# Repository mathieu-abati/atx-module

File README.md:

# RaspberryPi ATX PSU control module

With an ATX PSU powering a RaspberryPi, this circuit allows to control power ON / OFF from a single posh button.

More details [on the project official page](https://mathieu-abati.com/en/projects/atx-module/).

## Compatibility

| Board                  | Tested | Working    |
| ---------------------- | ------ | ---------- |
| RaspberryPi 3 Model B  | ✅     | ✅         |
| RaspberryPi 3 Model B+ | ✅     | ✅         |
| RaspberryPi 4 2GB      | ✅     | ✅         |
| RaspberryPi 5 2GB      | ✅     | ❌         |

On RaspberryPi 5, power supply from extension connector is more complicated and is not working as-is with this module.

## Additional resources

For simulation, 2N2222A spice model file is not provided here du to license restrictions. You can download it
[from onSemi website](https://www.onsemi.com/download/models/txt/2n2222a.lib.txt),
and save it as `models/2N2222A.lib`.

For PCB 3D view, you may want the `ATX Connector 24pin 90deg.stp` file. You can
find it from [Grabcad](https://grabcad.com/library/90-atx-connector-24-pins-1).

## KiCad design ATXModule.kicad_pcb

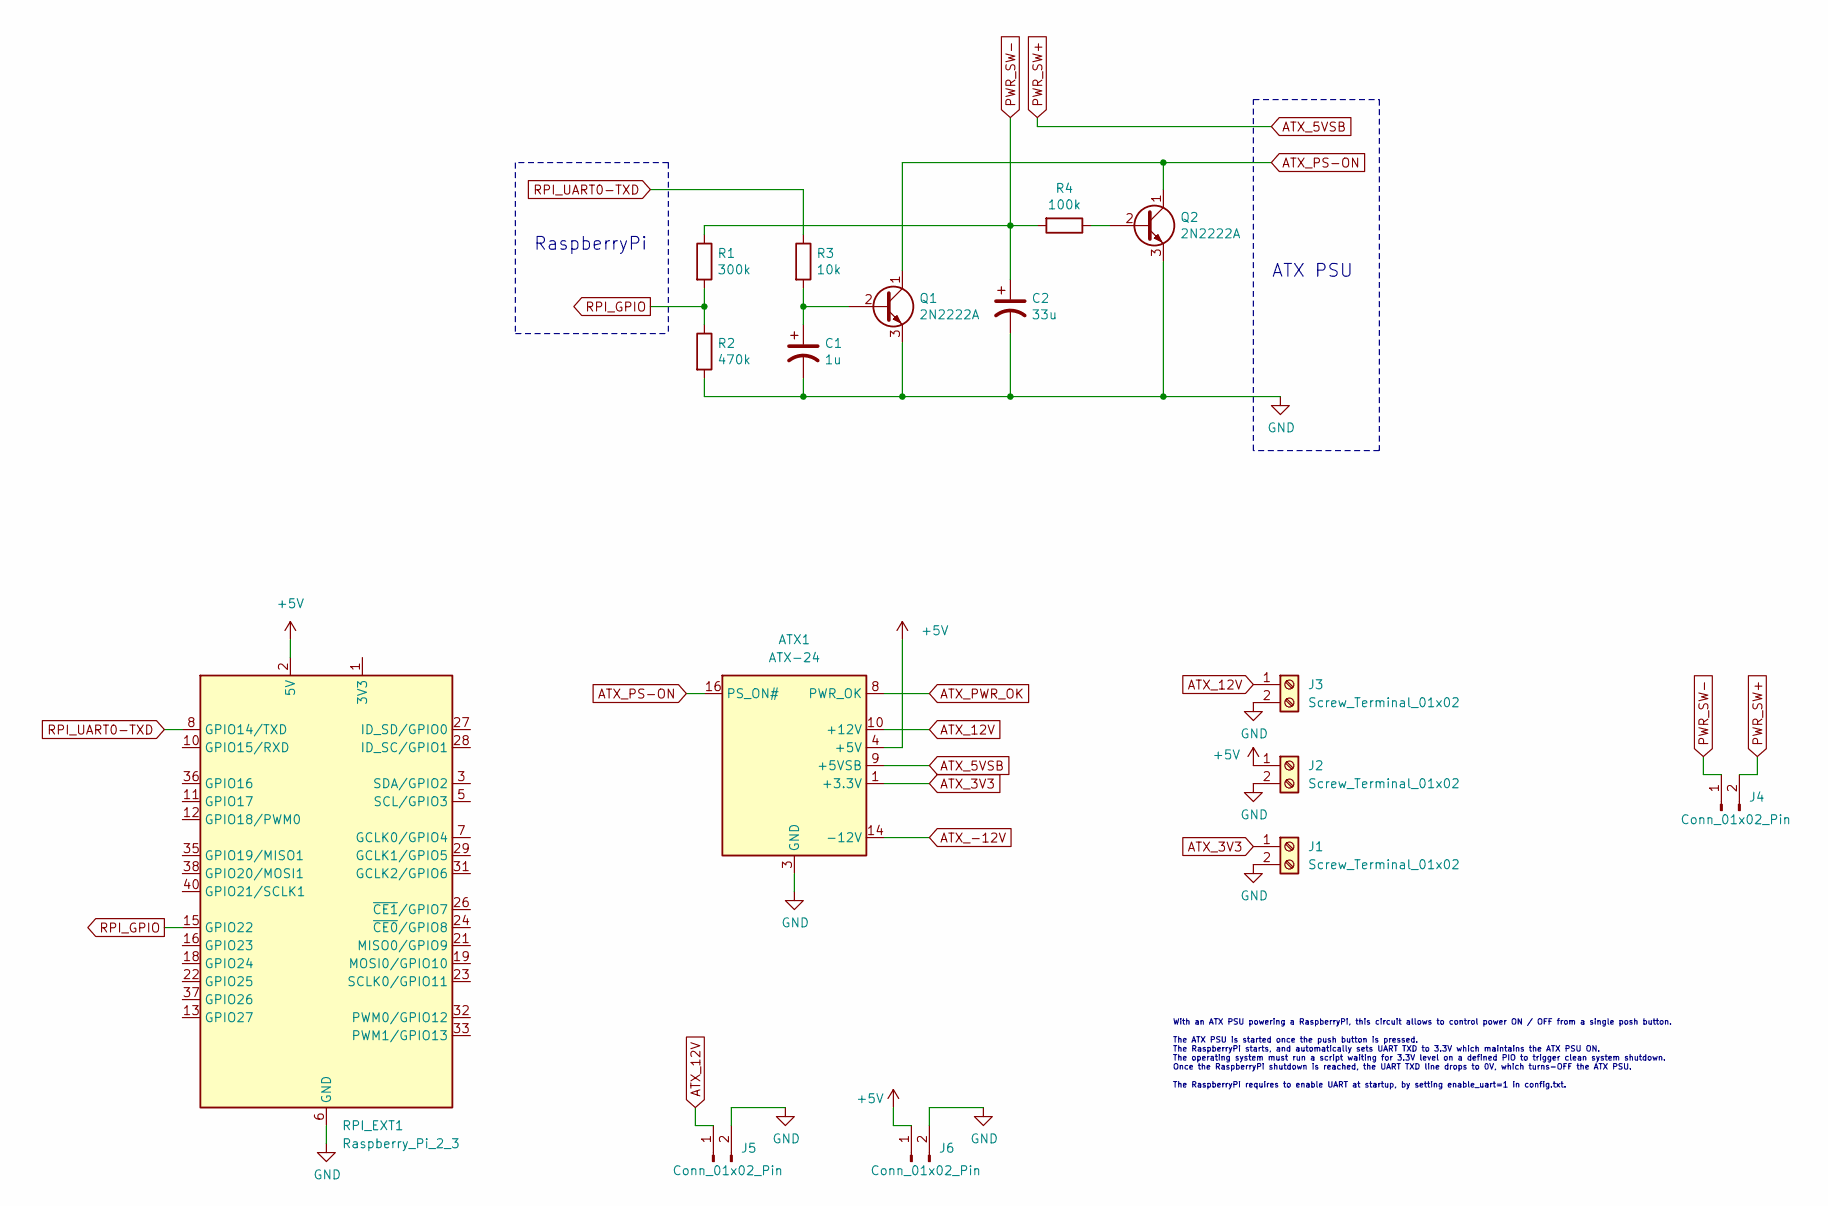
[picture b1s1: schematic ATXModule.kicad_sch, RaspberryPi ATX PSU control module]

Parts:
ATX1: ATX-24; Molex_Mini-Fit_Jr_5569-24A2_2x12_P4.20mm_Horizontal
C1: 1u; CP_Radial_D6.3mm_P2.50mm
C2: 33u; CP_Radial_D6.3mm_P2.50mm
J1, J2, J3: Screw_Terminal_01x02; TerminalBlock_Phoenix_MKDS-1,5-2_1x02_P5.00mm_Horizontal
J4: Conn_01x02_Pin; PinHeader_1x02_P2.54mm_Vertical
J5, J6: Conn_01x02_Pin; PinSocket_2x01_P2.54mm_Vertical_SMD
Q1, Q2: 2N2222A; TO-18-3
R1: 300k; R_Axial_DIN0207_L6.3mm_D2.5mm_P10.16mm_Horizontal
R2: 470k; R_Axial_DIN0207_L6.3mm_D2.5mm_P10.16mm_Horizontal
R3: 10k; R_Axial_DIN0207_L6.3mm_D2.5mm_P10.16mm_Horizontal
R4: 100k; R_Axial_DIN0207_L6.3mm_D2.5mm_P10.16mm_Horizontal
RPI_EXT1: Raspberry_Pi_2_3; PinSocket_2x20_P2.54mm_Vertical

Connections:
+5V: ATX1.4 (+5V), ATX1.6 (+5V), ATX1.21 (+5V), ATX1.22 (+5V), ATX1.23 (+5V), J2.1, J6.1, RPI_EXT1.2 (5V), RPI_EXT1.4 (5V)
ATX_3V3: ATX1.1 (+3.3V), ATX1.2 (+3.3V), ATX1.12 (+3.3V), ATX1.13 (+3.3V), J1.1
ATX_5VSB: ATX1.9 (+5VSB), J4.2
ATX_12V: ATX1.10 (+12V), ATX1.11 (+12V), J3.1, J5.1
ATX_-12V: ATX1.14 (-12V)
ATX_PS-ON: ATX1.16 (PS_ON#), Q1.1 (C), Q2.1 (C)
ATX_PWR_OK: ATX1.8 (PWR_OK)
GND: ATX1.3 (GND), ATX1.5 (GND), ATX1.7 (GND), ATX1.15 (GND), ATX1.17 (GND), ATX1.18 (GND), ATX1.19 (GND), ATX1.24 (GND), C1.2, C2.2, J1.2, J2.2, J3.2, J5.2, J6.2, Q1.3 (E), Q2.3 (E), R2.2, RPI_EXT1.6 (GND), RPI_EXT1.9 (GND), RPI_EXT1.14 (GND), RPI_EXT1.20 (GND), RPI_EXT1.25 (GND), RPI_EXT1.30 (GND), RPI_EXT1.34 (GND), RPI_EXT1.39 (GND)
unnamed: C1.1, Q1.2 (B), R3.2
unnamed: Q2.2 (B), R4.1
unnamed: RPI_EXT1.1 (3V3), RPI_EXT1.17 (3V3)
PWR_SW-: C2.1, J4.1, R1.1, R4.2
RPI_GPIO: R1.2, R2.1, RPI_EXT1.15 (GPIO22)
RPI_UART0-TXD: R3.1, RPI_EXT1.8 (GPIO14/TXD)

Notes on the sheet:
ATX PSU
With an ATX PSU powering a RaspberryPi, this circuit allows to control power ON / OFF from a single posh button. The ATX PSU is started once the push button is pressed. The RaspberryPi starts, and automatically sets UART TXD to 3.3V which maintains the ATX PSU ON. The operating system must run a sc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
RaspberryPi

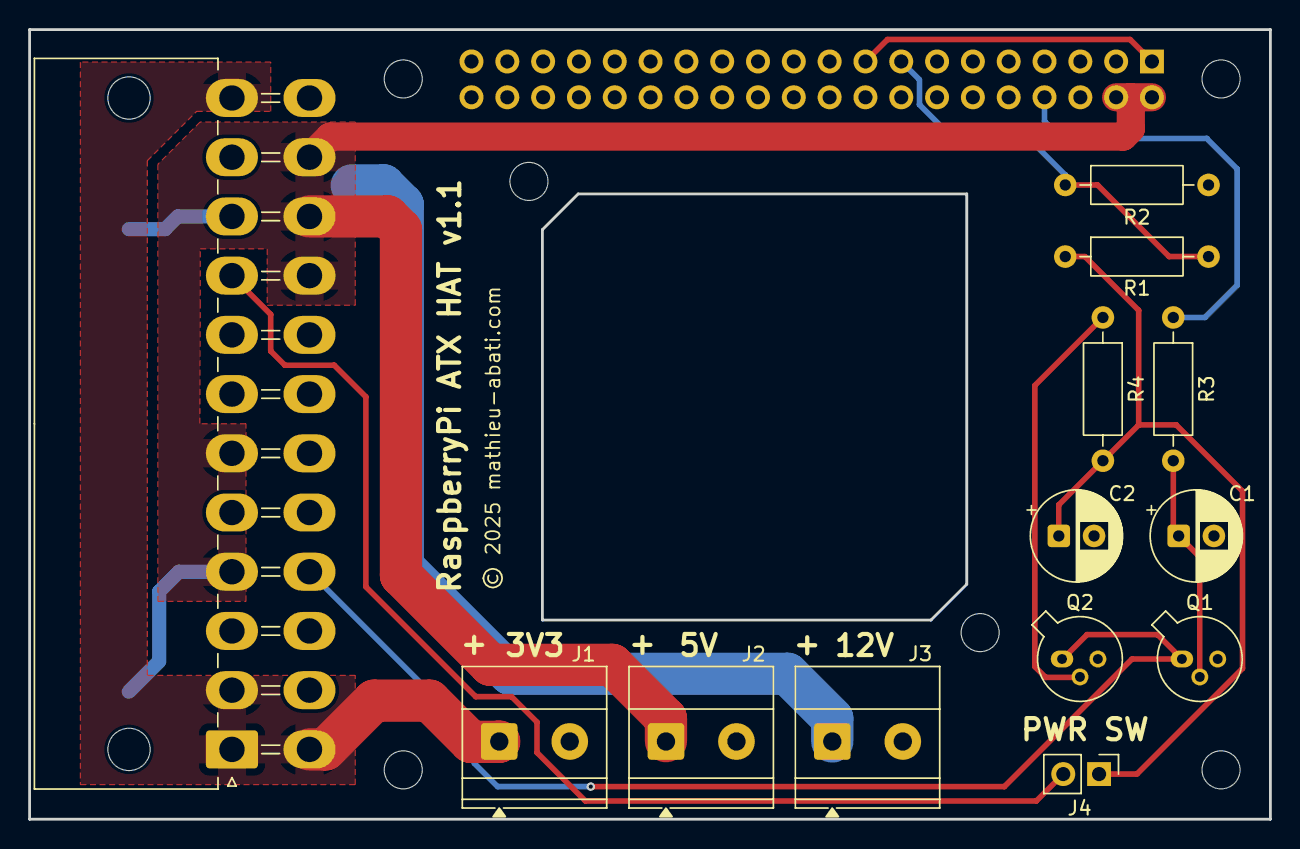
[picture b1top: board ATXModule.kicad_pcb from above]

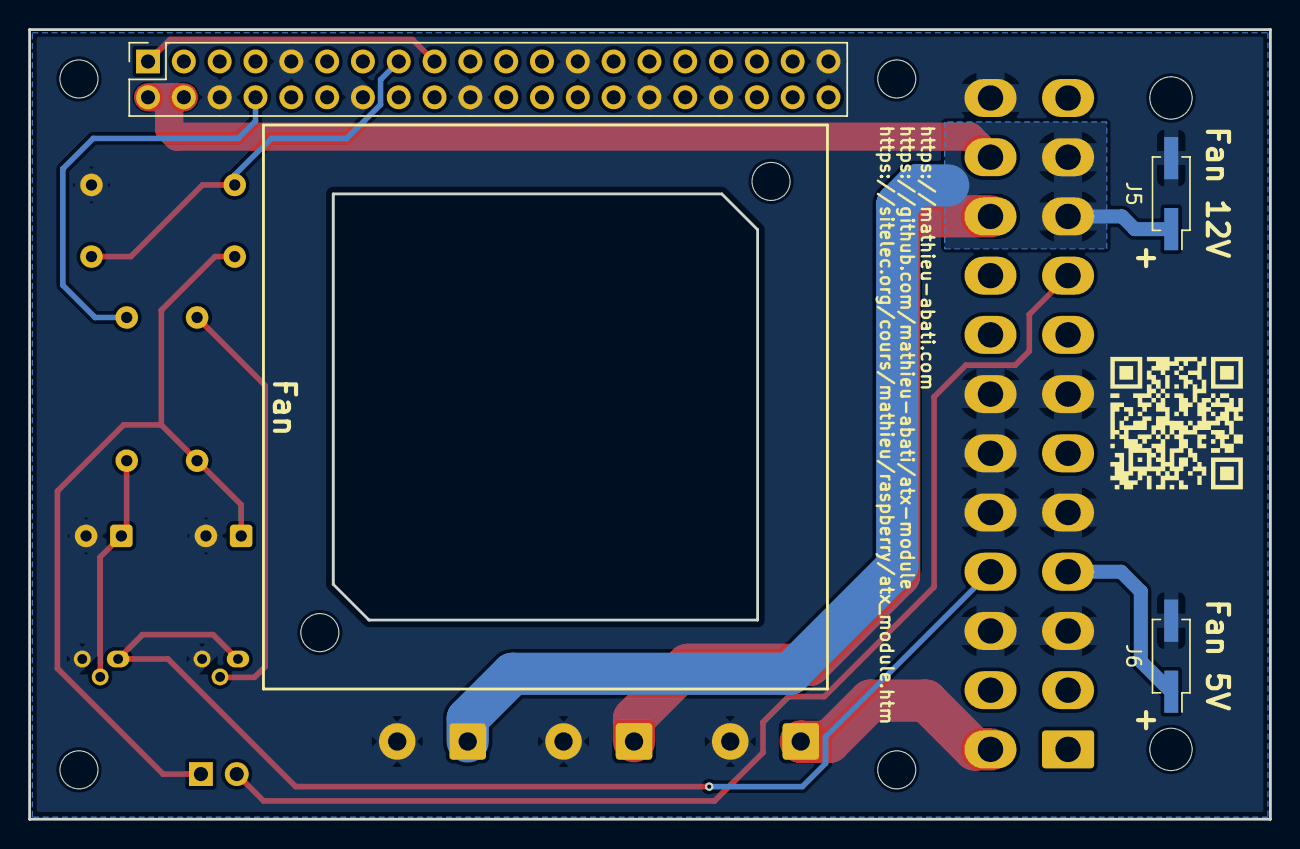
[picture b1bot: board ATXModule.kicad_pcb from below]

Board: 2 copper layers, 88.0 x 56.0 mm, 17 parts (4 on the bottom side), 12 nets.

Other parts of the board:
G1: LOGO; qr

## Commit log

2025-10-31 First release
2025-11-09 Create PCB
2025-11-10 PCB: improved some tracks placement
2025-11-10 Add project page QR code silkscreen
2025-11-10 Fix to support RaspberryPi 4
2025-11-10 Script: HOLD_TIME is now useless
2025-11-10 33u capacitor is enough
2025-11-10 Update PCB
2025-11-10 Update documentation
2025-11-11 Add fan footprint, screw holes and connectors
2025-11-11 Add PCB 3D rendered picture
2025-11-11 Update schema with fan connectors

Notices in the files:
ATXModule.kicad_pcb:
© 2025 mathieu-abati.com
